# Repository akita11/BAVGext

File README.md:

# BAVGext

M5Stack等でよく使われるネジ端子の「VH3.96-4P」に差し込んで固定することで延長するとともに、電源線を2種類のコネクタに引き出すものです。
[M5Stack BAVG2ソケット](https://www.switch-science.com/products/7234)と同じように使いますが、以下の点が異なります。
- 端子側がVH3.96コネクタ
- 電源線の端子が2mmピッチ(JST PHコネクタ等）と2.54mmピッチ（ピンソケットやJST XHコネクタ等)に引き出されている
- 信号線(A/B)間に抵抗などをとりつけられるスルーホールのパッドがある（RS485の終端抵抗など）

## Author 
Junichi AKita (akita@ifdl.jp, @akita11)

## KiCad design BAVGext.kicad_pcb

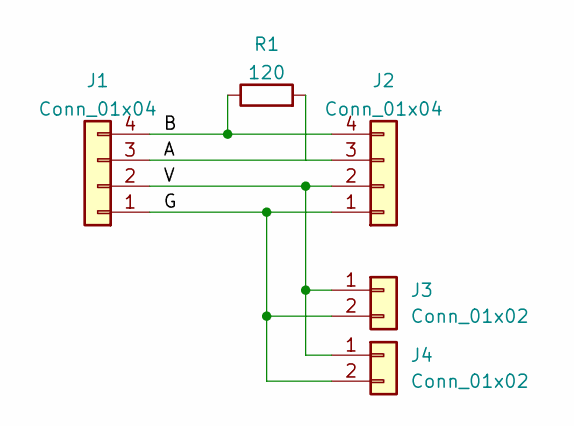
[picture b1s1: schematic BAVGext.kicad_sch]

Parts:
J1: Conn_01x04; JST_VH_S4P-VH_1x04_P3.96mm_Horizontal
J2: Conn_01x04; CON_BAVG
J3: Conn_01x02; JST_PH_B2B-PH-K_1x02_P2.00mm_Vertical
J4: Conn_01x02; JST_XH_B2B-XH-A_1x02_P2.50mm_Vertical
R1: 120; R_Axial_DIN0207_L6.3mm_D2.5mm_P2.54mm_Vertical

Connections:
/A: J1.3, J2.3, R1.2
/B: J1.4, J2.4, R1.1
/G: J1.1, J2.1, J3.2, J4.2
/V: J1.2, J2.2, J3.1, J4.1

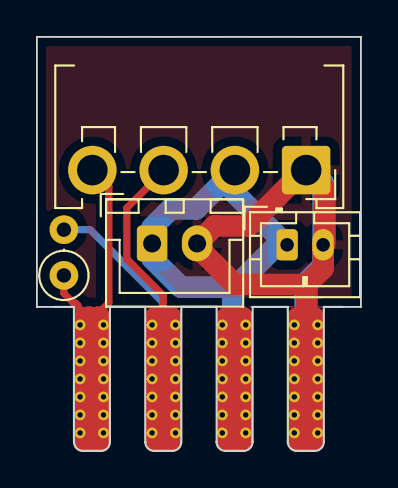
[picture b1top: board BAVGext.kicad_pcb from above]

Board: 2 copper layers, 18.0 x 23.0 mm, 5 parts (0 on the bottom side), 4 nets.

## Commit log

2023-07-22 add PCB files
2023-07-22 Update README.md (typo fix)
2023-07-30 replace files
